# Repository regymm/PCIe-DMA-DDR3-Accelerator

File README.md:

# PCIe-DMA-DDR3-accelerator

Under Construction!

Affordable Kintex-7 FPGA cards with DDR3 and PCIe have recently become accessible, but the open-source tooling and gateware ecosystem has not yet caught up.
This project aims to bridge the gap by having an open accelerator platform: a Raspberry Pi with PCIe root port, with 4 Kintex FPGA cards running fully open PCIe endpoint, DMA engine, and UberDDR3 controller.
Accelerators based on ZTachip will be implemented on the platform

## Status

### Task 1: Raspberry Pi CM5 + 4-Lane PCIe Baseboard
Schematics & PCB finished and sent to fabrication. 

[Board description](./1-baseboard/README.md)

The next step is board bring-up and test if the PCIe endpoint works under the PCIe switch. 

### Task 2: PCIe endpoint on Kintex 7

PCIe Gen2 x1 with OpenXC7 now works on Kintex 7 70t and 480t cards!

[pcie_7x repo with build files](https://github.com/regymm/pcie_7x) 

[OpenXC7 docker build file, with specified commit fully tested](https://github.com/FPGAOL-CE/osstoolchain-docker-things/tree/master/openxc7)

### Task 3: DMA over PCIe between FPGA and RPi CM5 Module
### Task 4: Porting ZTachip to OpenXC7
### Task 5: Integrated accelerator demonstration
### Task 6: ...
### Beyond code: Documentation in N4L

## Funding

 This project received funding through [NGI0 Entrust](https://nlnet.nl/entrust), a fund established by [NLnet](https://nlnet.nl) with financial support from the European Commission's [Next Generation Internet](https://ngi.eu) program. Learn more at the [NLnet project page](https://nlnet.nl/project/PCIe-DMA-DDR3-accelerator/).

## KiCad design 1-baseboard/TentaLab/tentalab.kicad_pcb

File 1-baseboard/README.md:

# Tentalab

*Interconnected PCIe FPGA accelerators*

#### Functions

The controller of this board is a RPi CM4/CM5 with PCIe x1. 

A PCIe switch (PI7C9X2G, Gen2 x4 to 4-lane Gen2 X1) bridges the PCIe into 4 PCIe x8 slots, each of them has one lane. 

The PCIe slots are designed for PCIe Kintex 7 accelerators like the [YPCB 480t](https://gist.github.com/regymm/4cfc4f174e3000f97810eb97d52f8ef3), but literally any FPGA cards can be supported. 

Since only 1 lane in the x8 slot are used, another 4 lanes are connected to QSFP connectors for custom protocols, SGMII ethernet, etc. The 3 lanes left are connected to the other 3 boards, forming a mesh connection. 

Designed with remote controlling in thought -- power enable, power switch, UART output, JTAG, and FPGA reset are accessible through pin headers. 

#### Board Preview

#### Manufacture

Designed for standard JLCPCB 4-layer board, impedance is for JLC7628 stacking. 

Now sent for manufacture and waiting for the boards. 

3D preview for SMT: 

#### Funding

This project is funded by the [NLNet Foundation](https://nlnet.nl) [NGI0 Commons Fund](https://nlnet.nl/project/PCIe-DMA-DDR3-accelerator/).

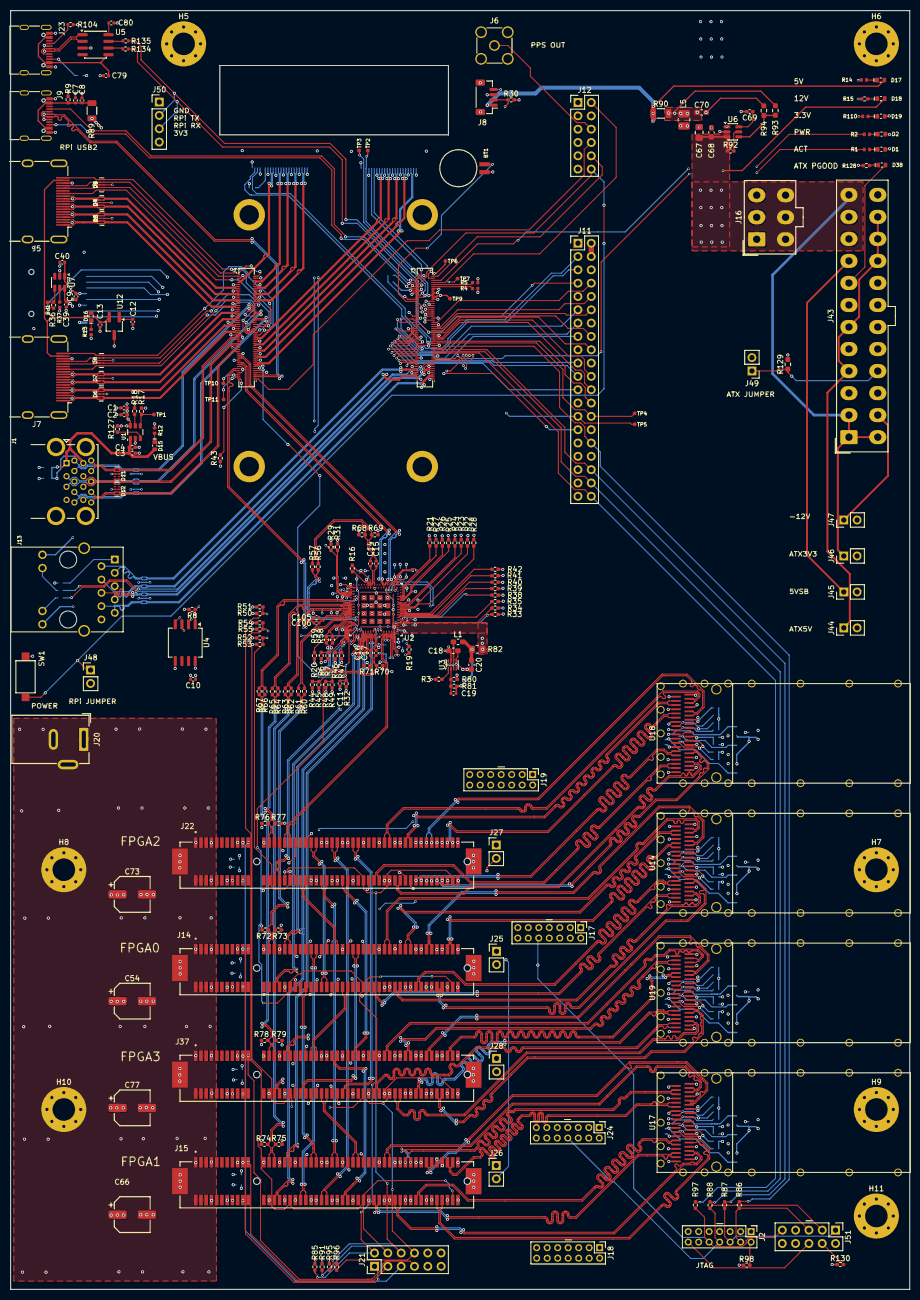
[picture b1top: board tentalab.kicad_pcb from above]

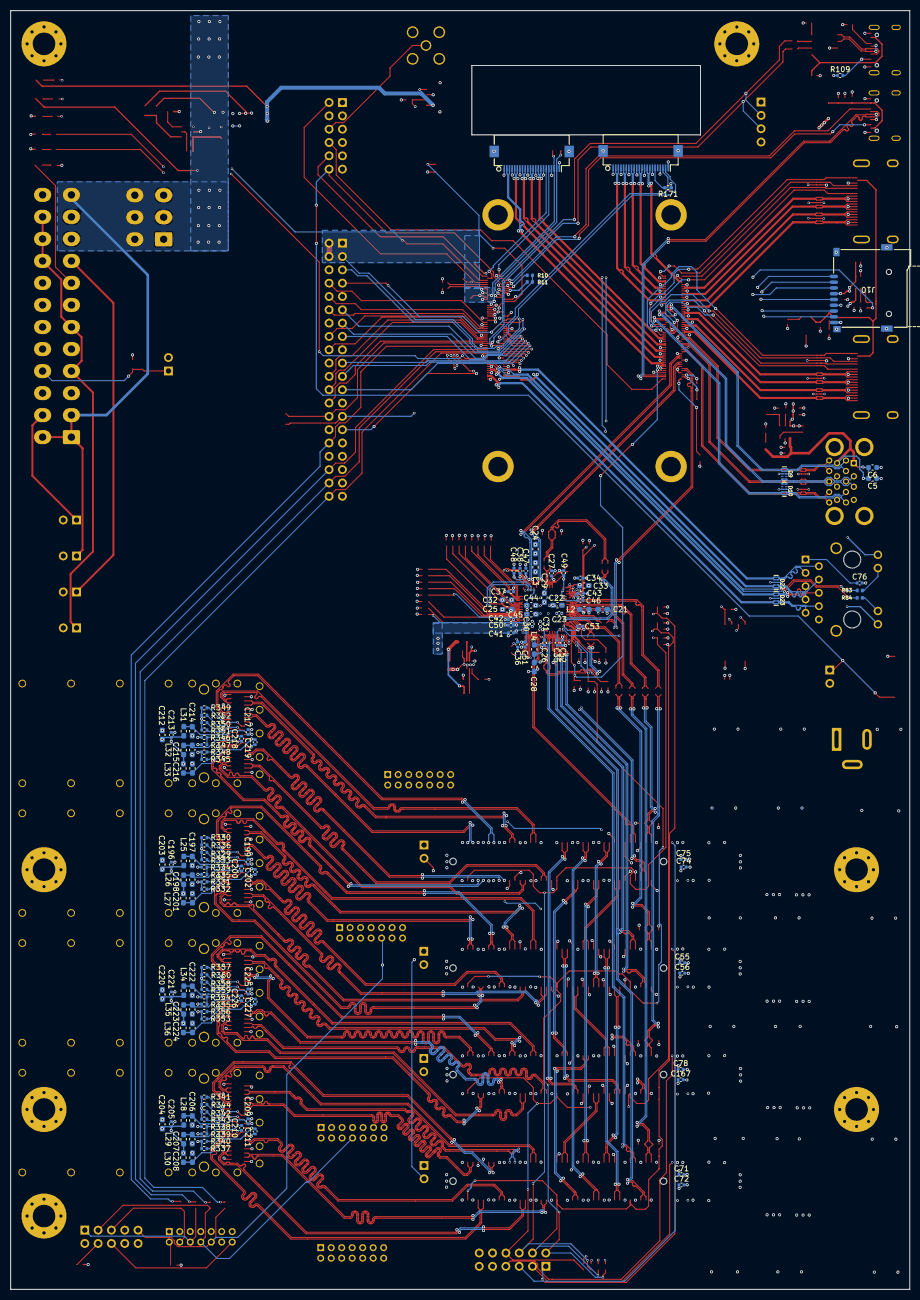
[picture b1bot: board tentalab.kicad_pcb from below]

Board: 4 copper layers, 171.4 x 243.8 mm, 360 parts (134 on the bottom side), 408 nets.

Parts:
A1: RPi CM5; CM5
BT1: Battery_MS621FE-FL11E
C1, C2, C3, C4, C9: C-4u7-0402; C_0402_1005Metric_Pad0.74x0.62mm_HandSolder
C5, C6: C-10u-0603; C_0603_1608Metric
C7, C8, C10, C12, C13, C14, C15, C16, C17, C23, C26, C27, C30, C31, C34, C35, C36, C37, C38, C41, C42, C43, C46, C47, C48, C49, C50, C51, C52, C53, C56, C72, C75, C105, C106, C167, C196, C199, C200, C202, C205, C209, C210, C211, C213, C217, C218, C219, C221, C225, C226, C227: 100n; C_0402_1005Metric
C11: 47pF/50V; C_0402_1005Metric
C18: 4.7u; C_0603_1608Metric_Pad1.08x0.95mm_HandSolder
C19: 120pF/50V; C_0402_1005Metric
C20: 10u; C_0603_1608Metric_Pad1.08x0.95mm_HandSolder
C21, C22, C24, C25, C28, C29, C32, C33, C44, C45, C197, C198, C201, C203, C204, C206, C207, C208, C212, C214, C215, C216, C220, C222, C223, C224: 22u; C_0603_1608Metric_Pad1.08x0.95mm_HandSolder
C39, C40: C-4u7-0402; C_0402_1005Metric
C54, C66, C73, C77: 100u 16V; CP_Elec_6.3x5.4
C55, C71, C74, C78: 10n; C_0402_1005Metric
C67: 10uF; C_0805_2012Metric_Pad1.18x1.45mm_HandSolder
C68: 100nF; C_0603_1608Metric_Pad1.08x0.95mm_HandSolder
C69: 100nF; C_0402_1005Metric_Pad0.74x0.62mm_HandSolder
C70: 10uF; C_0603_1608Metric_Pad1.08x0.95mm_HandSolder
C76: C-100n-0402; C_0402_1005Metric
C79, C80: 100nF; C_0402_1005Metric
D1, D2, D15, D16, D17, D18, D19, D38: LED-R-0603_KT-0603R; LED_0603_1608Metric_R
D3, D4, D5, D6, D7, D8, D9, D10, D11, D12, D22, D23: PUSB3F96X; SOT1176-1
H1, H2, H3, H4: Spacer_M2.5_H3mm_9774030151R
H5, H6, H7, H8, H9, H10, H11: MountingHole_Pad; MountingHole_4.3mm_M4_Pad_Via
J1: USB-A_USB-303WSD-BRY; USB-A_Receptacle_USB-303WSD-BRY
J2: JTAG_UPSTREAM; PinHeader_2x07_P2.00mm_Vertical
J3: CM5_1-100_3mm-stack; Conn_Socket_Hirose_DF40_2x50_DF40HC-3.0-100DS-0.4V
J4: CM5_101-200_3mm-stack; Conn_Socket_Hirose_DF40_2x50_DF40HC-3.0-100DS-0.4V
J5, J7: HDMI_A; HDMI_A_Molex_208658-1001_Horizontal
J6: Conn_Coaxial_Small; SMA_Amphenol_901-144_Vertical
J8: Conn_01x04; JST_SH_BM04B-SRSS-TB_1x04-1MP_P1.00mm_Vertical
J9: RPi USB2; USB_C_Receptacle_G-Switch_GT-USB-7010ASV
J10: Micro_SD_Card; SDMICRO_AT
J11: RPI_HEADER; PinHeader_2x20_P2.54mm_Vertical
J12: RPI_OPTIONS; PinHeader_2x06_P2.54mm_Vertical
J13: RJ45_HC612601A-M893-A
J14, J15, J22, J37: PCIe; PCIe x8 connector SMT AMPHENOL_10061913-102CLF
J16: 12V ATX; Molex_Mini-Fit_Jr_5566-06A_2x03_P4.20mm_Vertical
J17, J18, J19, J24: JTAG_0; PinHeader_2x07_P2.00mm_Vertical
J20: Jack-DC; BarrelJack_Wuerth_6941xx301002
J21: FPGA_RST_nPRSNT; PinHeader_2x06_P2.54mm_Vertical
J23: RPi UART; USB_C_Receptacle_G-Switch_GT-USB-7010ASV
J25, J26, J27, J28: JTAG_SKIP_0; PinHeader_1x02_P2.54mm_Vertical
J29, J30: Conn_01x22_Female; Hirose_FH12-22S-0.5SH_1x22-1MP_P0.50mm_Horizontal
J43: ATX-24; Molex_Mini-Fit_Jr_5566-24A_2x12_P4.20mm_Vertical
J44, J46: ATX5V; PinHeader_1x02_P2.54mm_Vertical
J45, J47: ATX5VSB; PinHeader_1x02_P2.54mm_Vertical
J48: PWR_JMPER; PinHeader_1x02_P2.54mm_Vertical
J49: ATXPWR_JMPER; PinHeader_1x02_P2.54mm_Vertical
J50: RPI_UART; PinHeader_1x04_P2.54mm_Vertical
J51: JTAG_UPSTREAM_2x5; PinHeader_2x05_P2.54mm_Vertical
L1: 470nH; L_0603_1608Metric_Pad1.05x0.95mm_HandSolder
L2, L3, L4: 120R@100MHz; L_0603_1608Metric_Pad1.05x0.95mm_HandSolder
L5: 4.7uH; L_1008_2520Metric_Pad1.43x2.20mm_HandSolder
L25, L26, L27, L28, L29, L30, L31, L32, L33, L34, L35, L36: 1uH; L_0603_1608Metric_Pad1.05x0.95mm_HandSolder
R1, R2, R12, R13, R14, R83, R84, R110: R-1k-0402; R_0402_1005Metric
R3, R8, R15, R29, R30, R31, R80, R81, R85, R91, R95, R96, R128: R-10k-0402; R_0402_1005Metric_Pad0.72x0.64mm_HandSolder
R4, R5, R10, R11: R-0R-0402; R_0402_1005Metric
R6, R7, R16, R17, R19, R20, R21, R22, R23, R24, R25, R26, R27, R28, R32, R33, R34, R35, R36, R38, R39, R40, R41, R42, R43, R44, R45, R46, R47, R48, R49, R50, R51, R52, R53, R54, R55, R56, R57, R58, R59, R60, R61, R62, R63, R64, R65, R66, R67, R68, R69, R70, R71, R72, R73, R74, R75, R76, R77, R78, R79, R86, R87, R88, R97, R98, R130: R-0R-0402; R_0402_1005Metric_Pad0.72x0.64mm_HandSolder
R9, R171: 2.2K 1%; R_0402_1005Metric_Pad0.72x0.64mm_HandSolder
R18, R127: R-2k2-0402; R_0402_1005Metric_Pad0.72x0.64mm_HandSolder
R37: R-10k-0402; R_0402_1005Metric
R82: R-10k-0402; R_0805_2012Metric_Pad1.20x1.40mm_HandSolder
R89, R90: 0R PWR; R_1206_3216Metric
R92: 10K; R_0402_1005Metric_Pad0.72x0.64mm_HandSolder
R93: 54.9K; R_0603_1608Metric_Pad0.98x0.95mm_HandSolder
R94, R129: 10K; R_0603_1608Metric_Pad0.98x0.95mm_HandSolder
R104, R109: 5.1K; R_0402_1005Metric
R134, R135: 33; R_0402_1005Metric
R329, R330, R331, R332, R333, R334, R335, R336, R337, R338, R339, R340, R341, R342, R343, R344, R345, R346, R347, R348, R349, R350, R351, R352, R353, R354, R355, R356, R357, R358, R359, R360: 4.7K; R_0402_1005Metric
SW1: PWR_BTN; SW_SPST_CK_RS282G05A3
TP1, TP2, TP3, TP4, TP5, TP6, TP7, TP8, TP9, TP10, TP11: TP_SMD_0.75mm
U1, U7: AP22615AWU-7; TSOT-23-6
U2: PI7C9X2G608ELBZXAE; XCVR_PI7C9X2G608ELBZXAE
U3: TPS62821DLC; Texas_VSON-HR-8_1.5x2mm_P0.5mm
U4: M93C86; SOIC-8_5.3x6.2mm_P1.27mm
U5: CH330N; SOIC-8_3.9x4.9mm_P1.27mm
U6: TPS563200; SOT-23-6
U12: RT9742SNGV; TSOT-23_HandSoldering
U14, U17, U18, U19: QSFP_Conn; QSFP_Conn_w_Cage

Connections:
+1V0_PCIE: C28.1, C44.1, C45.1, C46.1, C47.1, C48.1, C49.1, C50.1, C51.1, C52.1, C53.1, L4.1, R82.1, U2.A31 (VDDC), U2.AF34 (VDDC), U2.AP10 (VDDC), U2.AP32 (VDDC), U2.AR1 (VDDC), U2.AR7 (VDDC), U2.B4 (VDDC), U2.D2 (VDDC), U2.F2 (VDDC), U2.G35 (VDDC), U2.L (VDDC)
+1V0_PCIE_AVDD: C29.1, C30.1, C31.1, L4.2, U2.B (AVDD), U2.T (AVDD)
+3V3: C10.1, C18.1, C21.1, C24.1, C32.1, C33.1, C34.1, C35.1, C36.1, C37.1, C38.1, C39.2, C41.1, C42.1, C43.1, C55.1, C56.1, C71.1, C72.1, C74.1, C75.1, C78.1, C167.1, C196.1, C203.1, C204.1, C205.1, C212.1, C213.1, C220.1, C221.1, D1.2 (A), D2.2 (A), D19.2 (A), J3.84 (+3.3V_(Output)), J3.86 (+3.3V_(Output)), J11.1, J11.17, J13.11, J13.14, J14.A9 (+3.3V), J14.A10 (+3.3V), J14.B8 (+3.3V), J14.B10 (3.3Vaux), J15.A9 (+3.3V), J15.A10 (+3.3V), J15.B8 (+3.3V), J15.B10 (3.3Vaux), J21.11, J21.12, J22.A9 (+3.3V), J22.A10 (+3.3V), J22.B8 (+3.3V), J22.B10 (3.3Vaux), J29.22, J30.22, J37.A9 (+3.3V), J37.A10 (+3.3V), J37.B8 (+3.3V), J37.B10 (3.3Vaux), J50.4, L2.1, L3.1, L25.1, L26.1, L27.1, L28.1, L29.1, L30.1, L31.1, L32.1, L33.1, L34.1, L35.1, L36.1, R3.2, R6.1, R8.2, R11.1, R29.2, R30.2, R31.2, R32.1, R44.1, R46.1, R48.1, R50.1, R52.1, R54.1, R85.2, R91.2, R95.2, R96.2, R98.1, R130.1, R171.1, R329.1, R330.1, R331.1, R332.1, R333.1, R334.1, R336.1, R337.1, R338.1, R340.1, R341.1, R342.1, R343.1, R344.1, R345.1, R346.1, R348.1, R349.1, R350.1, R351.1, R352.1, R353.1, R354.1, R356.1, R357.1, R358.1, R359.1, R360.1, TP6.1 (1_1), U2.AC1 (VDDR), U2.AD2 (VDDR), U2.AH34 (VDDR), U2.AP2 (VDDR), U2.AP34 (VDDR), U2.AP35 (VDDR), U2.B2 (VDDR), U2.B30 (VDDR), U2.M2 (VDDR), U2.N1 (VDDR), U3.7 (VIN)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
+3V3_PCIE_AVDDH: C25.1, C26.1, C27.1, L3.2, U2.AR23 (AVDDH), U2.B16 (AVDDH), U2.V2 (AVDDH)
+3V3_PCIE_CVDDR: C22.1, C23.1, L2.2, U2.R (CVDDR)
+5V: C1.2, C2.2, D17.2 (A), J3.77 (+5V_(Input)), J3.79 (+5V_(Input)), J3.81 (+5V_(Input)), J3.83 (+5V_(Input)), J3.85 (+5V_(Input)), J3.87 (+5V_(Input)), J8.1, J11.2, J11.4, R89.1, R90.1, R127.2, TP9.1 (1_1), U1.6 (IN)
+12V: C54.1, C66.1, C67.1, C68.1, C73.1, C77.1, D18.2 (A), J14.A2 (+12V), J14.A3 (+12V), J14.B1 (+12V), J14.B2 (+12V), J14.B3 (+12V), J15.A2 (+12V), J15.A3 (+12V), J15.B1 (+12V), J15.B2 (+12V), J15.B3 (+12V), J16.1, J16.2, J16.3, J20.1, J22.A2 (+12V), J22.A3 (+12V), J22.B1 (+12V), J22.B2 (+12V), J22.B3 (+12V), J37.A2 (+12V), J37.A3 (+12V), J37.B1 (+12V), J37.B2 (+12V), J37.B3 (+12V), J43.10 (+12V), J43.11 (+12V), R92.1, U6.3 (VIN)
/+1V8_CM5: J3.88 (+1.8V_(Output)), J3.90 (+1.8V_(Output)), R10.1, TP7.1 (1_1)
/+5v: C12.1, U12.1 (IN)
/+VBUS: C3.2, C4.2, C5.2, C6.2, D15.2 (A), J1.1 (VBUS), J1.10 (VBUS), U1.1 (OUT)
/ATX3V3: J43.1 (+3.3V), J43.2 (+3.3V), J43.12 (+3.3V), J43.13 (+3.3V), J46.1
/ATX5V: J43.4 (+5V), J43.6 (+5V), J43.21 (+5V), J43.22 (+5V), J43.23 (+5V), J44.1
/ATX5VSB: J43.9 (+5VSB), J45.1
/ATXNeg12V: J43.14 (-12V), J47.1
/ATXPWROK: D38.2 (A), J43.8 (PWR_OK)
/CAM_GPIO0: J3.97 (CAM_GPIO0), J29.17
/CAM_GPIO1: J3.100 (CAM_GPIO1), J29.18
/CC1: J3.94 (CC1), J9.B5 (CC2)
/CC2: J3.96 (CC2), J9.A5 (CC1)
/ETH.D1+: D22.1 (CH1), D22.10 (CH1), J3.12 (Ethernet_Pair0_P), J13.2 (TD1+)
/ETH.D1-: D22.2 (CH2), D22.9 (CH2), J3.10 (Ethernet_Pair0_N), J13.3 (TD1-)
/ETH.D2+: D22.4 (CH3), D22.7 (CH3), J3.4 (Ethernet_Pair1_P), J13.4 (TD2+)
/ETH.D2-: D22.5 (CH4), D22.6 (CH4), J3.6 (Ethernet_Pair1_N), J13.7 (TD2-)
/ETH.D3+: D23.1 (CH1), D23.10 (CH1), J3.11 (Ethernet_Pair2_P), J13.5 (TD3+)
/ETH.D3-: D23.2 (CH2), D23.9 (CH2), J3.9 (Ethernet_Pair2_N), J13.6 (TD3-)
/ETH.D4+: D23.4 (CH3), D23.7 (CH3), J3.3 (Ethernet_Pair3_P), J13.8 (TD4+)
/ETH.D4-: D23.5 (CH4), D23.6 (CH4), J3.5 (Ethernet_Pair3_N), J13.9 (TD4-)
/FAN_PWM: J3.19 (FAN_PWM), J8.2, R30.1
/FAN_TACHO: J3.16 (FAN_TACHO), J8.4
/FPGA0_RST: J14.A11 (~PERST), J21.1, U2.AP4 (DWNRST_L[1])
/FPGA0_RX.+: J14.B14 (PETp0), U2.B28 (PERP[4])
/FPGA0_RX.-: J14.B15 (PETn0), U2.A29 (PERN[4])
/FPGA0_TX.+: J14.A16 (PERp0), U2.B26 (PETP[4])
/FPGA0_TX.-: J14.A17 (PERn0), U2.A27 (PETN[4])
/FPGA0_nPRSNT: J14.B17 (~PRSNT2), J14.B31 (~PRSNT2), J14.B48 (~PRSNT2), J21.2, R48.2, R49.2, R85.1, U2.C35 (~CLKREQ_L[3])
/FPGA1_RST: J15.A11 (~PERST), J21.3, U2.AP6 (DWNRST_L[2])
/FPGA1_RX.+: J15.B14 (PETp0), U2.B24 (PERP[5])
/FPGA1_RX.-: J15.B15 (PETn0), U2.A25 (PERN[5])
/FPGA1_TX.+: J15.A16 (PERp0), U2.B22 (PETP[5])
/FPGA1_TX.-: J15.A17 (PERn0), U2.A23 (PETN[5])
/FPGA1_nPRSNT: J15.B17 (~PRSNT2), J15.B31 (~PRSNT2), J15.B48 (~PRSNT2), J21.4, R50.2, R51.2, R91.1, U2.A35 (~CLKREQ_L[4])
/FPGA2_RST: J21.5, J22.A11 (~PERST), U2.AR3 (DWNRST_L[3])
/FPGA2_RX.+: J22.B14 (PETp0), U2.B10 (PERP[6])
/FPGA2_RX.-: J22.B15 (PETn0), U2.A9 (PERN[6])
/FPGA2_TX.+: J22.A16 (PERp0), U2.B12 (PETP[6])
/FPGA2_TX.-: J22.A17 (PERn0), U2.A11 (PETN[6])
/FPGA2_nPRSNT: J21.6, J22.B17 (~PRSNT2), J22.B31 (~PRSNT2), J22.B48 (~PRSNT2), R52.2, R53.2, R95.1, U2.B32 (~CLKREQ_L[5])
/FPGA3_RST: J21.7, J37.A11 (~PERST), U2.AP8 (DWNRST_L[4])
/FPGA3_RX.+: J37.B14 (PETp0), U2.B6 (PERP[7])
/FPGA3_RX.-: J37.B15 (PETn0), U2.A5 (PERN[7])
/FPGA3_TX.+: J37.A16 (PERp0), U2.B8 (PETP[7])
/FPGA3_TX.-: J37.A17 (PERn0), U2.A7 (PETN[7])
/FPGA3_nPRSNT: J21.8, J37.B17 (~PRSNT2), J37.B31 (~PRSNT2), J37.B48 (~PRSNT2), R54.2, R55.2, R96.1, U2.A33 (~CLKREQ_L[6])
/GPIO2: J3.58 (GPIO2), J11.3
/GPIO3: J3.56 (GPIO3), J11.5
/GPIO4: J3.54 (GPIO4), J11.7, J50.2, R135.1
/GPIO5: J3.34 (GPIO5), J11.29, J50.3, R134.1
/GPIO6: J3.30 (GPIO6), J11.31
/GPIO7: J3.37 (GPIO7), J11.26
/GPIO8: J3.39 (GPIO8), J11.24
/GPIO9: J3.40 (GPIO9), J11.21
/GPIO10: J3.44 (GPIO10), J11.19
/GPIO11: J3.38 (GPIO11), J11.23
/GPIO12: J3.31 (GPIO12), J11.32, R86.2
/GPIO13: J3.28 (GPIO13), J11.33
/GPIO14: J3.55 (GPIO14), J11.8
/GPIO15: J3.51 (GPIO15), J11.10
/GPIO16: J3.29 (GPIO16), J11.36, R87.2
/GPIO17: J3.50 (GPIO17), J11.11
/GPIO18: J3.49 (GPIO18), J11.12
/GPIO19: J3.26 (GPIO19), J11.35
/GPIO20: J3.27 (GPIO20), J11.38, R88.2
/GPIO21: J3.25 (GPIO21), J11.40, R97.2
/GPIO22: J3.46 (GPIO22), J11.15
/GPIO23: J3.47 (GPIO23), J11.16
/GPIO24: J3.45 (GPIO24), J11.18
/GPIO25: J3.41 (GPIO25), J11.22
/GPIO26: J3.24 (GPIO26), J11.37
/GPIO27: J3.48 (GPIO27), J11.13
/GPIO_VREF: J3.78 (GPIO_VREF), R10.2, R11.2
/HDMI_0.CEC: D5.1 (CH1), D5.10 (CH1), J4.51 (HDMI0_CEC), J5.13 (CEC)
/HDMI_0.CLK+: D4.4 (CH3), D4.7 (CH3), J4.88 (HDMI0_CLK_P), J5.10 (CK+)
/HDMI_0.CLK-: D4.5 (CH4), D4.6 (CH4), J4.90 (HDMI0_CLK_N), J5.12 (CK-)
/HDMI_0.D0+: D4.1 (CH1), D4.10 (CH1), J4.82 (HDMI0_TX0_P), J5.7 (D0+)
/HDMI_0.D0-: D4.2 (CH2), D4.9 (CH2), J4.84 (HDMI0_TX0_N), J5.9 (D0-)
/HDMI_0.D1+: D3.4 (CH3), D3.7 (CH3), J4.76 (HDMI0_TX1_P), J5.4 (D1+)
/HDMI_0.D1-: D3.5 (CH4), D3.6 (CH4), J4.78 (HDMI0_TX1_N), J5.6 (D1-)
/HDMI_0.D2+: D3.1 (CH1), D3.10 (CH1), J4.70 (HDMI0_TX2_P), J5.1 (D2+)
/HDMI_0.D2-: D3.2 (CH2), D3.9 (CH2), J4.72 (HDMI0_TX2_N), J5.3 (D2-)
/HDMI_0.HOTPLUG: D5.5 (CH4), D5.6 (CH4), J4.53 (HDMI0_HOTPLUG), J5.19 (HPD)
/HDMI_0.SCL: D5.2 (CH2), D5.9 (CH2), J4.100 (HDMI0_SCL), J5.15 (SCL)
/HDMI_0.SDA: D5.4 (CH3), D5.7 (CH3), J4.99 (HDMI0_SDA), J5.16 (SDA)
/HDMI_1.CEC: D8.1 (CH1), D8.10 (CH1), J4.49 (HDMI1_CEC), J7.13 (CEC)
/HDMI_1.CLK+: D7.4 (CH3), D7.7 (CH3), J4.64 (HDMI1_CLK_P), J7.10 (CK+)
/HDMI_1.CLK-: D7.5 (CH4), D7.6 (CH4), J4.66 (HDMI1_CLK_N), J7.12 (CK-)
/HDMI_1.D0+: D7.1 (CH1), D7.10 (CH1), J4.58 (HDMI1_TX0_P), J7.7 (D0+)
/HDMI_1.D0-: D7.2 (CH2), D7.9 (CH2), J4.60 (HDMI1_TX0_N), J7.9 (D0-)
/HDMI_1.D1+: D6.4 (CH3), D6.7 (CH3), J4.52 (HDMI1_TX1_P), J7.4 (D1+)
/HDMI_1.D1-: D6.5 (CH4), D6.6 (CH4), J4.54 (HDMI1_TX1_N), J7.6 (D1-)
/HDMI_1.D2+: D6.1 (CH1), D6.10 (CH1), J4.46 (HDMI1_TX2_P), J7.1 (D2+)
/HDMI_1.D2-: D6.2 (CH2), D6.9 (CH2), J4.48 (HDMI1_TX2_N), J7.3 (D2-)
/HDMI_1.HOTPLUG: D8.5 (CH4), D8.6 (CH4), J4.43 (HDMI1_HOTPLUG), J7.19 (HPD)
/HDMI_1.SCL: D8.2 (CH2), D8.9 (CH2), J4.47 (HDMI1_SCL), J7.15 (SCL)
/HDMI_1.SDA: D8.4 (CH3), D8.7 (CH3), J4.45 (HDMI1_SDA), J7.16 (SDA)
/HDMI_+5V: C13.1, D16.2 (A), J5.18 (+5V), J7.18 (+5V), U12.2 (OUT)
/ID_SC: J3.35 (ID_SC), J11.28, J30.20, TP4.1 (1_1)
/ID_SD: J3.36 (ID_SD), J11.27, J30.21, TP5.1 (1_1)
/ISET_SD3V3: R37.1, U7.5 (ISET)
/ISET_VBUS: R18.1, U1.5 (ISET)
/JTAG_SRST: J2.14, J51.6
/JTAG_TCK: J2.6, J17.6, J18.6, J19.6, J24.6, J51.1, R87.1
/JTAG_TDI: J2.10, J17.10, J25.2, J51.9, R97.1
/JTAG_TDI1: J17.8, J18.10, J25.1, J26.2
/JTAG_TDI2: J18.8, J19.10, J26.1, J27.2
/JTAG_TDI3: J19.8, J24.10, J27.1, J28.2
/JTAG_TDO: J2.8, J24.8, J28.1, J51.3, R88.1
/JTAG_TMS: J2.4, J17.4, J18.4, J19.4, J24.4, J51.5, R86.1
/JTAG_VREF: J2.2, R98.2
/LED_ACT: J3.15 (Ethernet_nLED3), R84.2
/LED_LINK: J3.17 (Ethernet_nLED2), R83.2
/MIPI_0.CLK+: J4.29 (MIPI0_C_P), J29.9
/MIPI_0.CLK-: J4.27 (MIPI0_C_N), J29.8
/MIPI_0.D0+: J4.17 (MIPI0_D0_P), J29.3
/MIPI_0.D0-: J4.15 (MIPI0_D0_N), J29.2
/MIPI_0.D1+: J4.23 (MIPI0_D1_P), J29.6
/MIPI_0.D1-: J4.21 (MIPI0_D1_N), J29.5
/MIPI_0.D2+: J4.35 (MIPI0_D2_P), J29.12
/MIPI_0.D2-: J4.33 (MIPI0_D2_N), J29.11
/MIPI_0.D3+: J4.41 (MIPI0_D3_P), J29.15
/MIPI_0.D3-: J4.39 (MIPI0_D3_N), J29.14
/MIPI_1.CLK+: J4.89 (MIPI1_C_P), J30.9
/MIPI_1.CLK-: J4.87 (MIPI1_C_N), J30.8
/MIPI_1.D0+: J4.77 (MIPI1_D0_P), J30.3
/MIPI_1.D0-: J4.75 (MIPI1_D0_N), J30.2
/MIPI_1.D1+: J4.83 (MIPI1_D1_P), J30.6
/MIPI_1.D1-: J4.81 (MIPI1_D1_N), J30.5
/MIPI_1.D2+: J4.95 (MIPI1_D2_P), J30.12
/MIPI_1.D2-: J4.93 (MIPI1_D2_N), J30.11
/MIPI_1.D3+: J4.96 (MIPI1_D3_P), J30.15
/MIPI_1.D3-: J4.94 (MIPI1_D3_N), J30.14
/PCIE X8 FPGA0/RX1.+: J14.A21 (PERp1), J15.B19 (PETp1)
/PCIE X8 FPGA0/RX1.-: J14.A22 (PERn1), J15.B20 (PETn1)
/PCIE X8 FPGA0/RX2.+: J14.A25 (PERp2), J22.B19 (PETp1)
/PCIE X8 FPGA0/RX2.-: J14.A26 (PERn2), J22.B20 (PETn1)
/PCIE X8 FPGA0/RX3.+: J14.A29 (PERp3), J37.B19 (PETp1)
/PCIE X8 FPGA0/RX3.-: J14.A30 (PERn3), J37.B20 (PETn1)
/PCIE X8 FPGA0/RX4.+: J14.A35 (PERp4), U14.17 (RX1p)
/PCIE X8 FPGA0/RX4.-: J14.A36 (PERn4), U14.18 (RX1n)
/PCIE X8 FPGA0/RX5.+: J14.A39 (PERp5), U14.22 (RX2p)
/PCIE X8 FPGA0/RX5.-: J14.A40 (PERn5), U14.21 (RX2n)
/PCIE X8 FPGA0/RX6.+: J14.A43 (PERp6), U14.14 (RX3p)
/PCIE X8 FPGA0/RX6.-: J14.A44 (PERn6), U14.15 (RX3n)
/PCIE X8 FPGA0/RX7.+: J14.A47 (PERp7), U14.25 (RX4p)
/PCIE X8 FPGA0/RX7.-: J14.A48 (PERn7), U14.24 (RX4n)
/PCIE X8 FPGA0/TX1.+: J14.B19 (PETp1), J15.A21 (PERp1)
/PCIE X8 FPGA0/TX1.-: J14.B20 (PETn1), J15.A22 (PERn1)
/PCIE X8 FPGA0/TX2.+: J14.B23 (PETp2), J22.A21 (PERp1)
/PCIE X8 FPGA0/TX2.-: J14.B24 (PETn2), J22.A22 (PERn1)
/PCIE X8 FPGA0/TX3.+: J14.B27 (PETp3), J37.A21 (PERp1)
/PCIE X8 FPGA0/TX3.-: J14.B28 (PETn3), J37.A22 (PERn1)
/PCIE X8 FPGA0/TX4.+: J14.B33 (PETp4), U14.36 (TX1p)
/PCIE X8 FPGA0/TX4.-: J14.B34 (PETn4), U14.37 (TX1n)
/PCIE X8 FPGA0/TX5.+: J14.B37 (PETp5), U14.3 (TX2p)
/PCIE X8 FPGA0/TX5.-: J14.B38 (PETn5), U14.2 (TX2n)
/PCIE X8 FPGA0/TX6.+: J14.B41 (PETp6), U14.33 (TX3p)
/PCIE X8 FPGA0/TX6.-: J14.B42 (PETn6), U14.34 (TX3n)
/PCIE X8 FPGA0/TX7.+: J14.B45 (PETp7), U14.6 (TX4p)
/PCIE X8 FPGA0/TX7.-: J14.B46 (PETn7), U14.5 (TX4n)
/PCIE X8 FPGA1/RX2.+: J15.A25 (PERp2), J22.B23 (PETp2)
/PCIE X8 FPGA1/RX2.-: J15.A26 (PERn2), J22.B24 (PETn2)
/PCIE X8 FPGA1/RX3.+: J15.A29 (PERp3), J37.B23 (PETp2)
/PCIE X8 FPGA1/RX3.-: J15.A30 (PERn3), J37.B24 (PETn2)
/PCIE X8 FPGA1/RX4.+: J15.A35 (PERp4), U17.17 (RX1p)
/PCIE X8 FPGA1/RX4.-: J15.A36 (PERn4), U17.18 (RX1n)
/PCIE X8 FPGA1/RX5.+: J15.A39 (PERp5), U17.22 (RX2p)
/PCIE X8 FPGA1/RX5.-: J15.A40 (PERn5), U17.21 (RX2n)
/PCIE X8 FPGA1/RX6.+: J15.A43 (PERp6), U17.14 (RX3p)
/PCIE X8 FPGA1/RX6.-: J15.A44 (PERn6), U17.15 (RX3n)
/PCIE X8 FPGA1/RX7.+: J15.A47 (PERp7), U17.25 (RX4p)
/PCIE X8 FPGA1/RX7.-: J15.A48 (PERn7), U17.24 (RX4n)
/PCIE X8 FPGA1/TX2.+: J15.B23 (PETp2), J22.A25 (PERp2)
/PCIE X8 FPGA1/TX2.-: J15.B24 (PETn2), J22.A26 (PERn2)
/PCIE X8 FPGA1/TX3.+: J15.B27 (PETp3), J37.A25 (PERp2)
/PCIE X8 FPGA1/TX3.-: J15.B28 (PETn3), J37.A26 (PERn2)
/PCIE X8 FPGA1/TX4.+: J15.B33 (PETp4), U17.36 (TX1p)
/PCIE X8 FPGA1/TX4.-: J15.B34 (PETn4), U17.37 (TX1n)
/PCIE X8 FPGA1/TX5.+: J15.B37 (PETp5), U17.3 (TX2p)
/PCIE X8 FPGA1/TX5.-: J15.B38 (PETn5), U17.2 (TX2n)
/PCIE X8 FPGA1/TX6.+: J15.B41 (PETp6), U17.33 (TX3p)
/PCIE X8 FPGA1/TX6.-: J15.B42 (PETn6), U17.34 (TX3n)
/PCIE X8 FPGA1/TX7.+: J15.B45 (PETp7), U17.6 (TX4p)
/PCIE X8 FPGA1/TX7.-: J15.B46 (PETn7), U17.5 (TX4n)
/PCIE X8 FPGA2/RX3.+: J22.A29 (PERp3), J37.B27 (PETp3)
/PCIE X8 FPGA2/RX3.-: J22.A30 (PERn3), J37.B28 (PETn3)
/PCIE X8 FPGA2/RX4.+: J22.A35 (PERp4), U18.17 (RX1p)
/PCIE X8 FPGA2/RX4.-: J22.A36 (PERn4), U18.18 (RX1n)
/PCIE X8 FPGA2/RX5.+: J22.A39 (PERp5), U18.22 (RX2p)
/PCIE X8 FPGA2/RX5.-: J22.A40 (PERn5), U18.21 (RX2n)
/PCIE X8 FPGA2/RX6.+: J22.A43 (PERp6), U18.14 (RX3p)
/PCIE X8 FPGA2/RX6.-: J22.A44 (PERn6), U18.15 (RX3n)
/PCIE X8 FPGA2/RX7.+: J22.A47 (PERp7), U18.25 (RX4p)
/PCIE X8 FPGA2/RX7.-: J22.A48 (PERn7), U18.24 (RX4n)
/PCIE X8 FPGA2/TX3.+: J22.B27 (PETp3), J37.A29 (PERp3)
/PCIE X8 FPGA2/TX3.-: J22.B28 (PETn3), J37.A30 (PERn3)
/PCIE X8 FPGA2/TX4.+: J22.B33 (PETp4), U18.36 (TX1p)
/PCIE X8 FPGA2/TX4.-: J22.B34 (PETn4), U18.37 (TX1n)
/PCIE X8 FPGA2/TX5.+: J22.B37 (PETp5), U18.3 (TX2p)
/PCIE X8 FPGA2/TX5.-: J22.B38 (PETn5), U18.2 (TX2n)
/PCIE X8 FPGA2/TX6.+: J22.B41 (PETp6), U18.33 (TX3p)
/PCIE X8 FPGA2/TX6.-: J22.B42 (PETn6), U18.34 (TX3n)
/PCIE X8 FPGA2/TX7.+: J22.B45 (PETp7), U18.6 (TX4p)
/PCIE X8 FPGA2/TX7.-: J22.B46 (PETn7), U18.5 (TX4n)
/PCIE X8 FPGA3/RX4.+: J37.A35 (PERp4), U19.17 (RX1p)
/PCIE X8 FPGA3/RX4.-: J37.A36 (PERn4), U19.18 (RX1n)
/PCIE X8 FPGA3/RX5.+: J37.A39 (PERp5), U19.22 (RX2p)
/PCIE X8 FPGA3/RX5.-: J37.A40 (PERn5), U19.21 (RX2n)
/PCIE X8 FPGA3/RX6.+: J37.A43 (PERp6), U19.14 (RX3p)
/PCIE X8 FPGA3/RX6.-: J37.A44 (PERn6), U19.15 (RX3n)
/PCIE X8 FPGA3/RX7.+: J37.A47 (PERp7), U19.25 (RX4p)
/PCIE X8 FPGA3/RX7.-: J37.A48 (PERn7), U19.24 (RX4n)
/PCIE X8 FPGA3/TX4.+: J37.B33 (PETp4), U19.36 (TX1p)
/PCIE X8 FPGA3/TX4.-: J37.B34 (PETn4), U19.37 (TX1n)
/PCIE X8 FPGA3/TX5.+: J37.B37 (PETp5), U19.3 (TX2p)
/PCIE X8 FPGA3/TX5.-: J37.B38 (PETn5), U19.2 (TX2n)
/PCIE X8 FPGA3/TX6.+: J37.B41 (PETp6), U19.33 (TX3p)
/PCIE X8 FPGA3/TX6.-: J37.B42 (PETn6), U19.34 (TX3n)
/PCIE X8 FPGA3/TX7.+: J37.B45 (PETp7), U19.6 (TX4p)
/PCIE X8 FPGA3/TX7.-: J37.B46 (PETn7), U19.5 (TX4n)
/PCIE_EECK: U2.AK34 (EECK), U4.2 (SCLK)
/PCIE_EECS: R8.1, U2.AN35 (EECS_L), U4.1 (CS)
/PCIE_EEDI: U2.AM34 (EEDI), U4.3 (DI)
/PCIE_EEDO: U2.AL35 (EEDO), U4.4 (DO)
/PCIE_SCL: J3.80 (SCL0), J29.20, R29.1, TP2.1 (1_1), U2.AG35 (SCL_I2C)
/PCIE_SDA: J3.82 (SDA0), J29.21, R31.1, TP3.1 (1_1), U2.AJ35 (SDA_I2C)
/PCIe.REFCLK+: C106.1, J4.10 (PCIe_CLK_P)
/PCIe.REFCLK-: C105.1, J4.12 (PCIe_CLK_N)
/PCIe.REFCLK_PIN+: C106.2, U2.T34 (REFCLKIP)
/PCIe.REFCLK_PIN-: C105.2, U2.U35 (REFCLKIN)
/PCIe.RX0+: J4.16 (PCIe_RX_P), U2.AP12 (PETP[0])
/PCIe.RX0-: J4.18 (PCIe_RX_N), U2.AR13 (PETN[0])
/PCIe.TX0+: J4.22 (PCIe_TX_P), U2.AR9 (PERP[0])
/PCIe.TX0-: J4.24 (PCIe_TX_N), U2.AR11 (PERN[0])
/PCIe_PWR_EN: J4.6 (PCIE_PWR_EN), TP10.1 (1_1)
/PMIC_EN: J3.99 (PMIC_ENABLE), J12.10
/PPS_OUT: J3.18 (Ethernet_SYNC_OUT), J6.1 (In), J12.6
/PWR_BTN: J3.92 (PWR_BUT), J12.12, J48.1, SW1.1
/QSFP1/Vcc1: C201.1, C202.1, L27.2, U14.30 (Vcc1)
/QSFP1/VccRX: C198.1, C200.1, L26.2, U14.10 (VccRX)
/QSFP1/VccTX: C197.1, C199.1, L25.2, U14.29 (VccTX)
/QSFP2/Vcc1: C208.1, C211.1, L30.2, U17.30 (Vcc1)
/QSFP2/VccRX: C207.1, C210.1, L29.2, U17.10 (VccRX)
/QSFP2/VccTX: C206.1, C209.1, L28.2, U17.29 (VccTX)
/QSFP3/Vcc1: C216.1, C219.1, L33.2, U18.30 (Vcc1)
/QSFP3/VccRX: C215.1, C218.1, L32.2, U18.10 (VccRX)
/QSFP3/VccTX: C214.1, C217.1, L31.2, U18.29 (VccTX)
/QSFP4/Vcc1: C224.1, C227.1, L36.2, U19.30 (Vcc1)
/QSFP4/VccRX: C223.1, C226.1, L35.2, U19.10 (VccRX)
/QSFP4/VccTX: C222.1, C225.1, L34.2, U19.29 (VccTX)
/REFCLK1_PIN+: C14.2, U2.AR21 (REFCLKN[0])
/REFCLK1_PIN-: C15.2, U2.AR19 (REFCLKP[0])
/REFCLK2_PIN+: C17.2, U2.A19 (REFCLKN[1])
/REFCLK2_PIN-: C16.2, U2.A21 (REFCLKP[1])
/REFCLKO1.+: C14.1, R56.2, R68.1
/REFCLKO1.-: C15.1, R57.2, R69.1
/REFCLKO1_PIN+: R56.1, U2.K34 (REFCLKOP[1])
/REFCLKO1_PIN-: R57.1, U2.M34 (REFCLKON[1])
/REFCLKO2.+: C17.1, R58.2, R70.1
/REFCLKO2.-: C16.1, R59.2, R71.1
/REFCLKO2_PIN+: R58.1, U2.L35 (REFCLKOP[2])
/REFCLKO2_PIN-: R59.1, U2.N35 (REFCLKON[2])
/REFCLKO3.+: J14.A13 (REFCLK+), R60.2, R72.1
/REFCLKO3.-: J14.A14 (REFCLK-), R61.2, R73.1
/REFCLKO3_PIN+: R60.1, U2.P34 (REFCLKOP[3])
/REFCLKO3_PIN-: R61.1, U2.R35 (REFCLKON[3])
/REFCLKO4.+: J15.A13 (REFCLK+), R62.2, R74.1
/REFCLKO4.-: J15.A14 (REFCLK-), R63.2, R75.1
/REFCLKO4_PIN+: R62.1, U2.V34 (REFCLKOP[4])
/REFCLKO4_PIN-: R63.1, U2.W35 (REFCLKON[4])
/REFCLKO5.+: J22.A13 (REFCLK+), R64.2, R76.1
/REFCLKO5.-: J22.A14 (REFCLK-), R65.2, R77.1
/REFCLKO5_PIN+: R64.1, U2.Y34 (REFCLKOP[5])
/REFCLKO5_PIN-: R65.1, U2.AA35 (REFCLKON[5])
/REFCLKO7.+: J37.A13 (REFCLK+), R66.2, R78.1
/REFCLKO7.-: J37.A14 (REFCLK-), R67.2, R79.1
/REFCLKO7_PIN+: R66.1, U2.AB34 (REFCLKOP[7])
/REFCLKO7_PIN-: R67.1, U2.AD34 (REFCLKON[7])
/RPiUART_VBUS: C79.2, J23.A4 (VBUS), J23.A9 (VBUS), J23.B4 (VBUS), J23.B9 (VBUS), U5.5 (VCC)
/RPiUSB2_VBUS: C7.1, C8.1, J9.A4 (VBUS), J9.A9 (VBUS), J9.B4 (VBUS), J9.B9 (VBUS), R9.1, R89.2
/SD_+3V3: C9.2, C40.2, J10.4 (VDD), U7.1 (OUT)
/SD_CARD.CLK: J3.57 (SD_CLK), J10.5 (CLK)
/SD_CARD.CMD: J3.62 (SD_CMD), J10.3 (CMD)
/SD_CARD.DAT0: J3.63 (SD_DAT0), J10.7 (DAT0)
/SD_CARD.DAT1: J3.67 (SD_DAT1), J10.8 (DAT1)
/SD_CARD.DAT2: J3.69 (SD_DAT2), J10.1 (DAT2)
/SD_CARD.DAT3: J3.61 (SD_DAT3), J10.2 (DAT3/CD)
/SD_PWR_ON: J3.75 (SD_PWR_ON), R36.1
/SWG_LVL: R6.2, R7.2, U2.H34 (SWG_LVL)
/USB.D+: J4.5 (USB2_P), J9.A6 (D+), J9.B6 (D+)
/USB.D-: J4.3 (USB2_N), J9.A7 (D-), J9.B7 (D-)
/USBOTG: J4.1 (USB_OTG_ID), J12.8
/USB_SS_0.D+: D12.1 (CH1), D12.10 (CH1), J1.12 (D+), J4.34 (USB3-0-D_P)
/USB_SS_0.D-: D11.5 (CH4), D11.6 (CH4), J1.11 (D-), J4.36 (USB3-0-D_N)
/USB_SS_0.RX+: D12.4 (CH3), D12.7 (CH3), J1.15 (SSRX+), J4.30 (USB3-0-RX_P)
/USB_SS_0.RX-: D12.5 (CH4), D12.6 (CH4), J1.14 (SSRX-), J4.28 (USB3-0-RX_N)
/USB_SS_0.TX+: D11.1 (CH1), D11.10 (CH1), J1.18 (SSTX+), J4.42 (USB3-0-TX_P)
/USB_SS_0.TX-: D11.2 (CH2), D11.9 (CH2), J1.17 (SSTX-), J4.40 (USB3-0-TX_N)
/USB_SS_1.D+: D10.1 (CH1), D10.10 (CH1), J1.3 (D+), J4.63 (USB3-1-D_P)
/USB_SS_1.D-: D9.5 (CH4), D9.6 (CH4), J1.2 (D-), J4.65 (USB3-1-D_N)
/USB_SS_1.RX+: D10.4 (CH3), D10.7 (CH3), J1.6 (SSRX+), J4.59 (USB3-1-RX_P)
/USB_SS_1.RX-: D10.5 (CH4), D10.6 (CH4), J1.5 (SSRX-), J4.57 (USB3-1-RX_N)
/USB_SS_1.TX+: D9.1 (CH1), D9.10 (CH1), J1.9 (SSTX+), J4.71 (USB3-1-TX_P)
/USB_SS_1.TX-: D9.2 (CH2), D9.9 (CH2), J1.8 (SSTX-), J4.69 (USB3-1-TX_N)
/VBAT: BT1.1 (+), J3.76 (VBAT)
/VBUS_EN: J4.11 (VBUS_EN), R17.1
/~BT_DIS: J3.91 (BT_nDisable), R5.2
/~CLKREQ_L_1: R44.2, R45.2, U2.E35 (~CLKREQ_L[1])
/~CLKREQ_L_2: R46.2, R47.2, U2.F34 (~CLKREQ_L[2])
/~EEPROM_WP: J3.20 (EEPROM_nWP), J12.4
/~LED_ACT: J3.21 (LED_nACT), R1.1
/~LED_PWR: J3.95 (LED_nPWR), R2.1
/~PCIe_CLKREQ: J4.2 (PCIe_nCLKREQ), R43.2
/~PCIe_PERST: C11.1, J4.9 (PCIe_nRST), R32.2, U2.D34 (PERST_L)
/~PCIe_WAKE: J4.4 (PCIE_nWAKE), TP11.1 (1_1)
/~RPIBOOT: J3.93 (nRPIBOOT), J12.2
/~WiFi_DIS: J3.89 (WiFi_nDisable), R4.2
GND: BT1.2 (-), C1.1, C2.1, C3.1, C4.1, C5.1, C6.1, C7.2, C8.2, C9.1, C10.2, C11.2, C12.2, C13.2, C18.2, C20.2, C21.2, C22.2, C23.2, C24.2, C25.2, C26.2, C27.2, C28.2, C29.2, C30.2, C31.2, C32.2, C33.2, C34.2, C35.2, C36.2, C37.2, C38.2, C39.1, C40.1, C41.2, C42.2, C43.2, C44.2, C45.2, C46.2, C47.2, C48.2, C49.2, C50.2, C51.2, C52.2, C53.2, C54.2, C55.2, C56.2, C66.2, C67.2, C68.2, C70.2, C71.2, C72.2, C73.2, C74.2, C75.2, C76.1, C77.2, C78.2, C79.1, C80.2, C167.2, C196.2, C197.2, C198.2, C199.2, C200.2, C201.2, C202.2, C203.2, C204.2, C205.2, C206.2, C207.2, C208.2, C209.2, C210.2, C211.2, C212.2, C213.2, C214.2, C215.2, C216.2, C217.2, C218.2, C219.2, C220.2, C221.2, C222.2, C223.2, C224.2, C225.2, C226.2, C227.2, D3.3 (GND), D3.8 (GND), D4.3 (GND), D4.8 (GND), D5.3 (GND), D5.8 (GND), D6.3 (GND), D6.8 (GND), D7.3 (GND), D7.8 (GND), D8.3 (GND), D8.8 (GND), D9.3 (GND), D9.8 (GND), D10.3 (GND), D10.8 (GND), D11.3 (GND), D11.8 (GND), D12.3 (GND), D12.8 (GND), D22.3 (GND), D22.8 (GND), D23.3 (GND), D23.8 (GND), H1.1, H2.1, H3.1, H4.1, H5.1 (1_1), H6.1 (1_1), H7.1 (1_1), H8.1 (1_1), H9.1 (1_1), H10.1 (1_1), H11.1 (1_1), J1.4 (GND), J1.7 (DRAIN)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
unnamed: C19.2, C20.1, L1.2, R81.2, R82.2
unnamed: C70.1, L5.2, R90.2, R93.1
unnamed: D1.1 (C), R1.2
unnamed: D2.1 (C), R2.2
unnamed: D15.1 (C), R12.2
unnamed: D16.1 (C), R13.2
unnamed: D17.1 (C), R14.2
unnamed: D18.1 (C), R15.2
unnamed: D19.1 (C), R110.2
unnamed: D38.1 (C), R128.2
unnamed: C76.2, J13.1 (CT)
unnamed: J13.12, R83.1
unnamed: J13.13, R84.1
unnamed: J23.A5 (CC1), R104.2
unnamed: J23.B5 (CC2), R109.2
unnamed: J30.17, R171.2
unnamed: J43.16 (PS_ON#), J49.1, R129.1
unnamed: J51.4, R130.2
unnamed: R17.2, TP1.1 (1_1), U1.4 (EN)
unnamed: R127.1, U1.3 (~FLG)
unnamed: R21.2, U2.AH2 (CLKBUF_PD)
unnamed: R22.1, U2.Y2 (DBO[1])
unnamed: R23.1, U2.AA1 (DBO[2])
unnamed: R33.2, U2.H2 (GPIO[0])
unnamed: R34.2, U2.J1 (GPIO[1])
unnamed: R35.2, U2.K2 (GPIO[2])
unnamed: R38.2, U2.L1 (GPIO[3])
unnamed: R39.2, U2.P2 (GPIO[4])
unnamed: R40.2, U2.R1 (GPIO[5])
unnamed: R41.2, U2.T2 (GPIO[6])
unnamed: R42.2, U2.U1 (GPIO[7])
unnamed: R20.2, U2.J35 (IREF)
unnamed: R28.2, U2.W1 (PL_512B/DBO[0])
unnamed: R16.1, U2.AP22 (REXTGND[0])
unnamed: R19.1, U2.B14 (REXTGND[1])
unnamed: R16.2, U2.AP24 (REXT[0])
unnamed: R19.2, U2.A13 (REXT[1])
unnamed: R24.2, U2.AB2 (UPS_PORTSEL[0]/DBO[3])
unnamed: R25.2, U2.AE1 (UPS_PORTSEL[1]/DBO[4])
unnamed: R26.2, U2.AF2 (UPS_PORTSEL[2])
unnamed: R27.2, U2.AG1 (UPS_PORTSEL[3])
unnamed: R3.1, U3.1 (EN)
unnamed: C19.1, R80.1, R81.1, U3.2 (FB)
unnamed: L1.1, U3.6 (SW)
unnamed: R135.2, U5.7 (RXD)
unnamed: R134.2, U5.6 (TXD)
unnamed: J23.A6 (D+), J23.B6 (D+), U5.1 (UD+)
unnamed: J23.A7 (D-), J23.B7 (D-), U5.2 (UD-)
unnamed: C80.1, U5.8 (V3)
unnamed: R92.2, U6.5 (EN)
unnamed: C69.2, L5.1, U6.2 (SW)
unnamed: C69.1, U6.6 (VBST)
unnamed: R93.2, R94.1, U6.4 (VFB)
unnamed: R36.2, TP8.1 (1_1), U7.4 (EN)
unnamed: R333.2, U14.28 (IntL)
unnamed: R332.2, U14.31 (LPMode)
unnamed: R336.2, U14.27 (ModPrsL)
unnamed: R331.2, U14.8 (ModSelL)
unnamed: R334.2, R335.1, U14.9 (ResetL)
unnamed: R329.2, U14.11 (SCL)
unnamed: R330.2, U14.12 (SDA)
unnamed: R343.2, U17.28 (IntL)
unnamed: R337.2, U17.31 (LPMode)
unnamed: R344.2, U17.27 (ModPrsL)
unnamed: R340.2, U17.8 (ModSelL)
unnamed: R338.2, R339.1, U17.9 (ResetL)
unnamed: R342.2, U17.11 (SCL)
unnamed: R341.2, U17.12 (SDA)
unnamed: R351.2, U18.28 (IntL)
unnamed: R345.2, U18.31 (LPMode)
unnamed: R352.2, U18.27 (ModPrsL)
unnamed: R348.2, U18.8 (ModSelL)
unnamed: R346.2, R347.1, U18.9 (ResetL)
unnamed: R350.2, U18.11 (SCL)
unnamed: R349.2, U18.12 (SDA)
unnamed: R359.2, U19.28 (IntL)
unnamed: R353.2, U19.31 (LPMode)
unnamed: R360.2, U19.27 (ModPrsL)
unnamed: R356.2, U19.8 (ModSelL)
unnamed: R354.2, R355.1, U19.9 (ResetL)
unnamed: R358.2, U19.11 (SCL)
unnamed: R357.2, U19.12 (SDA)

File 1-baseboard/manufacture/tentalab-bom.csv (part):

Designator,Qty,Comment,DNP,Exclude from BOM,Exclude from Board,Footprint,Datasheet,LCSC
BT1,1,Battery_MS621FE-FL11E,DNP,,,cm5-module-Library:Battery_MS621FE-FL11E,https://www.sii.co.jp/en/me/datasheets/ms-rechargeable/ms621fe/,
"C1,C2,C3,C4,C9",5,C-4u7-0402,,,,Capacitor_SMD:C_0402_1005Metric_Pad0.74x0.62mm_HandSolder,https://lcsc.com/datasheet/lcsc_datasheet_2304140030_Samsung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,C23733
"C5,C6",2,C-10u-0603,,,,Capacitor_SMD:C_0603_1608Metric,https://www.lcsc.com/datasheet/C96446.pdf,C96446
"C7,C8,C10,C12,C13,C14,C15,C16,C17,C23,C26,C27,C30,C31,C34,C35,C36,C37,C38,C41,C42,C43,C46,C47,C48,C49,C50,C51,C52,C53,C56,C72,C75,C105,C106,C167,C196,C199,C200,C202,C205,C209,C210,C211,C213,C217,C218,C219,C221,C225,C226,C227",52,100n,,,,Capacitor_SMD:C_0402_1005Metric,https://search.murata.co.jp/Ceramy/image/img/A01X/G101/ENG/G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,
C11,1,47pF/50V,,,,Capacitor_SMD:C_0402_1005Metric,https://search.murata.co.jp/Ceramy/image/img/A01X/G101/ENG/G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,
C18,1,4.7u,,,,Capacitor_SMD:C_0603_1608Metric_Pad1.08x0.95mm_HandSolder,https://search.murata.co.jp/Ceramy/image/img/A01X/G101/ENG/G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,
C19,1,120pF/50V,,,,Capacitor_SMD:C_0402_1005Metric,https://search.murata.co.jp/Ceramy/image/img/A01X/G101/ENG/G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,
C20,1,10u,,,,Capacitor_SMD:C_0603_1608Metric_Pad1.08x0.95mm_HandSolder,https://search.murata.co.jp/Ceramy/image/img/A01X/G101/ENG/G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,
"C21,C22,C24,C25,C28,C29,C32,C33,C44,C45,C197,C198,C201,C203,C204,C206,C207,C208,C212,C214,C215,C216,C220,C222,C223,C224",26,22u,,,,Capacitor_SMD:C_0603_1608Metric_Pad1.08x0.95mm_HandSolder,https://search.murata.co.jp/Ceramy/image/img/A01X/G101/ENG/G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,
"C39,C40",2,C-4u7-0402,,,,Capacitor_SMD:C_0402_1005Metric,https://lcsc.com/datasheet/lcsc_datasheet_2304140030_Samsung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,C23733
"C54,C66,C73,C77",4,100u 16V,,,,Capacitor_SMD:CP_Elec_6.3x5.4,,
"C55,C71,C74,C78",4,10n,,,,Capacitor_SMD:C_0402_1005Metric,https://search.murata.co.jp/Ceramy/image/img/A01X/G101/ENG/G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,
C67,1,10uF,,,,Capacitor_SMD:C_0805_2012Metric_Pad1.18x1.45mm_HandSolder,,
C68,1,100nF,,,,Capacitor_SMD:C_0603_1608Metric_Pad1.08x0.95mm_HandSolder,,
C69,1,100nF,,,,Capacitor_SMD:C_0402_1005Metric_Pad0.74x0.62mm_HandSolder,,
C70,1,10uF,,,,Capacitor_SMD:C_0603_1608Metric_Pad1.08x0.95mm_HandSolder,,
C76,1,C-100n-0402,,,,Capacitor_SMD:C_0402_1005Metric,https://lcsc.com/datasheet/lcsc_datasheet_2304140030_Samsung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,C307331
"C79,C80",2,100nF,,,,Capacitor_SMD:C_0402_1005Metric,,
"D1,D2,D15,D16,D17,D18,D19,D38",8,LED-R-0603_KT-0603R,,,,cm5-module-Library:LED_0603_1608Metric_R,https://lcsc.com/datasheet/lcsc_datasheet_2507101606_Hubei-K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,C2286
"D3,D4,D5,D6,D7,D8,D9,D10,D11,D12,D22,D23",12,PUSB3F96X,,,,cm5-module-Library:SOT1176-1,https://mouser.com/datasheet/2/916/PUSB3F96-1600324.pdf,C478121
"H1,H2,H3,H4",4,Spacer_M2.5_H3mm_9774030151R,,,,cm5-module-Library:Spacer_M2.5_H3mm_9774030151R,https://www.we-online.com/components/products/datasheet/9774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,
J1,1,USB-A_USB-303WSD-BRY,,,,cm5-module-Library:USB-A_Receptacle_USB-303WSD-BRY,https://lcsc.com/datasheet/lcsc_datasheet_2411220306_XUNPU-U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,C2895028
J2,1,JTAG_UPSTREAM,,,,Connector_PinHeader_2.00mm:PinHeader_2x07_P2.00mm_Vertical,,
J3,1,CM5_1-100_3mm-stack,,,,cm5-module-Library:Conn_Socket_Hirose_DF40_2x50_DF40HC-3.0-100DS-0.4V,https://lcsc.com/datasheet/lcsc_datasheet_2410121810_HRS-DF4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,C424649
J4,1,CM5_101-200_3mm-stack,,,,cm5-module-Library:Conn_Socket_Hirose_DF40_2x50_DF40HC-3.0-100DS-0.4V,https://lcsc.com/datasheet/lcsc_datasheet_2410121810_HRS-DF4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,C424649
"J5,J7",2,HDMI_A,,,,Connector_Video:HDMI_A_Molex_208658-1001_Horizontal,https://en.wikipedia.org/wiki/HDMI,
J6,1,Conn_Coaxial_Small,DNP,,,Connector_Coaxial:SMA_Amphenol_901-144_Vertical,,
J8,1,Conn_01x04,,,,CM5IOLibrary:JST_SH_BM04B-SRSS-TB_1x04-1MP_P1.00mm_Vertical,,
J9,1,RPi USB2,,,,Connector_USB:USB_C_Receptacle_G-Switch_GT-USB-7010ASV,https://www.usb.org/sites/default/files/documents/usb_type-c.zip,
J10,1,Micro_SD_Card,,,,memblaze2qmtech:SDMICRO_AT,https://www.we-online.com/components/products/datasheet/6930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,
J11,1,RPI_HEADER,,,,Connector_PinHeader_2.54mm:PinHeader_2x20_P2.54mm_Vertical,https://www.toby.co.uk/uploads/publications/1673.pdf,
J12,1,RPI_OPTIONS,,,,Connector_PinHeader_2.54mm:PinHeader_2x06_P2.54mm_Vertical,,
J13,1,RJ45_HC612601A-M893-A,,,,cm5-module-Library:RJ45_HC612601A-M893-A,https://lcsc.com/datasheet/lcsc_datasheet_2504101957_HCTL-HC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,C3021368
"J14,J15,J22,J37",4,PCIe,,,,memblaze2qmtech:PCIe x8 connector SMT AMPHENOL_10061913-102CLF,http://www.ritrontek.com/uploadfile/2016/1026/20161026105231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,
J16,1,12V ATX,,,,Connector_Molex:Molex_Mini-Fit_Jr_5566-06A_2x03_P4.20mm_Vertical,,
"J17,J18,J19,J24",4,JTAG_0,,,,Connector_PinHeader_2.00mm:PinHeader_2x07_P2.00mm_Vertical,,
J20,1,Jack-DC,,,,Connector_BarrelJack:BarrelJack_Wuerth_6941xx301002,,
J21,1,FPGA_RST_nPRSNT,,,,Connector_PinHeader_2.54mm:PinHeader_2x06_P2.54mm_Vertical,,
J23,1,RPi UART,,,,Connector_USB:USB_C_Receptacle_G-Switch_GT-USB-7010ASV,https://www.usb.org/sites/default/files/documents/usb_type-c.zip,
"J25,J26,J27,J28",4,JTAG_SKIP_0,,,,Connector_PinHeader_2.54mm:PinHeader_1x02_P2.54mm_Vertical,,
"J29,J30",2,Conn_01x22_Female,,,,CM5IOLibrary:Hirose_FH12-22S-0.5SH_1x22-1MP_P0.50mm_Horizontal,https://www.hirose.com/product/document?clcode=&productname=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,
J43,1,ATX-24,,,,Connector_Molex:Molex_Mini-Fit_Jr_5566-24A_2x12_P4.20mm_Vertical,https://www.intel.com/content/dam/www/public/us/en/documents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,
"J44,J46",2,ATX5V,,,,Connector_PinHeader_2.54mm:PinHeader_1x02_P2.54mm_Vertical,,
"J45,J47",2,ATX5VSB,,,,Connector_PinHeader_2.54mm:PinHeader_1x02_P2.54mm_Vertical,,
J48,1,PWR_JMPER,,,,Connector_PinHeader_2.54mm:PinHeader_1x02_P2.54mm_Vertical,,
J49,1,ATXPWR_JMPER,,,,Connector_PinHeader_2.54mm:PinHeader_1x02_P2.54mm_Vertical,,
J50,1,RPI_UART,,,,Connector_PinHeader_2.54mm:PinHeader_1x04_P2.54mm_Vertical,,
J51,1,JTAG_UPSTREAM_2x5,,,,Connector_PinHeader_2.54mm:PinHeader_2x05_P2.54mm_Vertical,,
L1,1,470nH,,,,Inductor_SMD:L_0603_1608Metric_Pad1.05x0.95mm_HandSolder,,
"L2,L3,L4",3,120R@100MHz,,,,Inductor_SMD:L_0603_1608Metric_Pad1.05x0.95mm_HandSolder,,
L5,1,4.7uH,,,,Inductor_SMD:L_1008_2520Metric_Pad1.43x2.20mm_HandSolder,,
"L25,L26,L27,L28,L29,L30,L31,L32,L33,L34,L35,L36",12,1uH,,,,Inductor_SMD:L_0603_1608Metric_Pad1.05x0.95mm_HandSolder,,
"R1,R2,R12,R13,R14,R83,R84,R110",8,R-1k-0402,,,,cm5-module-Library:R_0402_1005Metric,https://lcsc.com/datasheet/lcsc_datasheet_2411221126_UNI-ROY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,C11702
R3,1,5.1k,,,,Resistor_SMD:R_0402_1005Metric_Pad0.72x0.64mm_HandSolder,https://lcsc.com/datasheet/lcsc_datasheet_2411221126_UNI-ROY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,C25744
"R4,R5,R10",3,R-0R-0402,DNP,,,cm5-module-Library:R_0402_1005Metric,https://lcsc.com/datasheet/lcsc_datasheet_2411221126_UNI-ROY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,C17168
"R6,R8,R29,R31",4,5.1K,,,,Resistor_SMD:R_0402_1005Metric_Pad0.72x0.64mm_HandSolder,"https://lcsc.com/datasheet/lcsc_datasheet_2411221126_UNI-ROY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,https://lcsc.com/datasheet/lcsc_datasheet_2411221126_UNI-ROY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","C17168,C25744"
"R7,R44,R46,R48,R50,R52,R54",7,R-0R-0402,DNP,,,Resistor_SMD:R_0402_1005Metric_Pad0.72x0.64mm_HandSolder,https://lcsc.com/datasheet/lcsc_datasheet_2411221126_UNI-ROY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,C17168
"R9,R171",2,2.2K 1%,,,,Resistor_SMD:R_0402_1005Metric_Pad0.72x0.64mm_HandSolder,https://fscdn.rohm.com/en/products/databook/datasheet/passiv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,
R11,1,R-0R-0402,,,,cm5-module-Library:R_0402_1005Metric,https://lcsc.com/datasheet/lcsc_datasheet_2411221126_UNI-ROY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,C17168
"R15,R30,R85,R91,R95,R96,R127,R128",8,R-10k-0402,,,,Resistor_SMD:R_0402_1005Metric_Pad0.72x0.64mm_HandSolder,"https://lcsc.com/datasheet/lcsc_datasheet_2411221126_UNI-ROY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,https://lcsc.com/datasheet/lcsc_datasheet_2411221126_UNI-ROY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","C25744,C25879"
"R16,R19",2,1.43K,,,,Resistor_SMD:R_0402_1005Metric_Pad0.72x0.64mm_HandSolder,https://lcsc.com/datasheet/lcsc_datasheet_2411221126_UNI-ROY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,C17168
"R17,R36,R86,R87,R88,R97,R98,R130",8,R-0R-0402,,,,Resistor_SMD:R_0402_1005Metric_Pad0.72x0.64mm_HandSolder,https://lcsc.com/datasheet/lcsc_datasheet_2411221126_UNI-ROY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,C17168
R18,1,R-2k2-0402,,,,Resistor_SMD:R_0402_1005Metric_Pad0.72x0.64mm_HandSolder,https://lcsc.com/datasheet/lcsc_datasheet_2411221126_UNI-ROY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,C25879
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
